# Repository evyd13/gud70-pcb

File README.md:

# Gud70 PCB

This is a replacement PCB for the Uniqey C70. Manufacturing files are included.

Some boards do not come with the LED seperator thingy, to prevent light bleed, so there is one that can be 3d printed as well.

Please read the license before use.

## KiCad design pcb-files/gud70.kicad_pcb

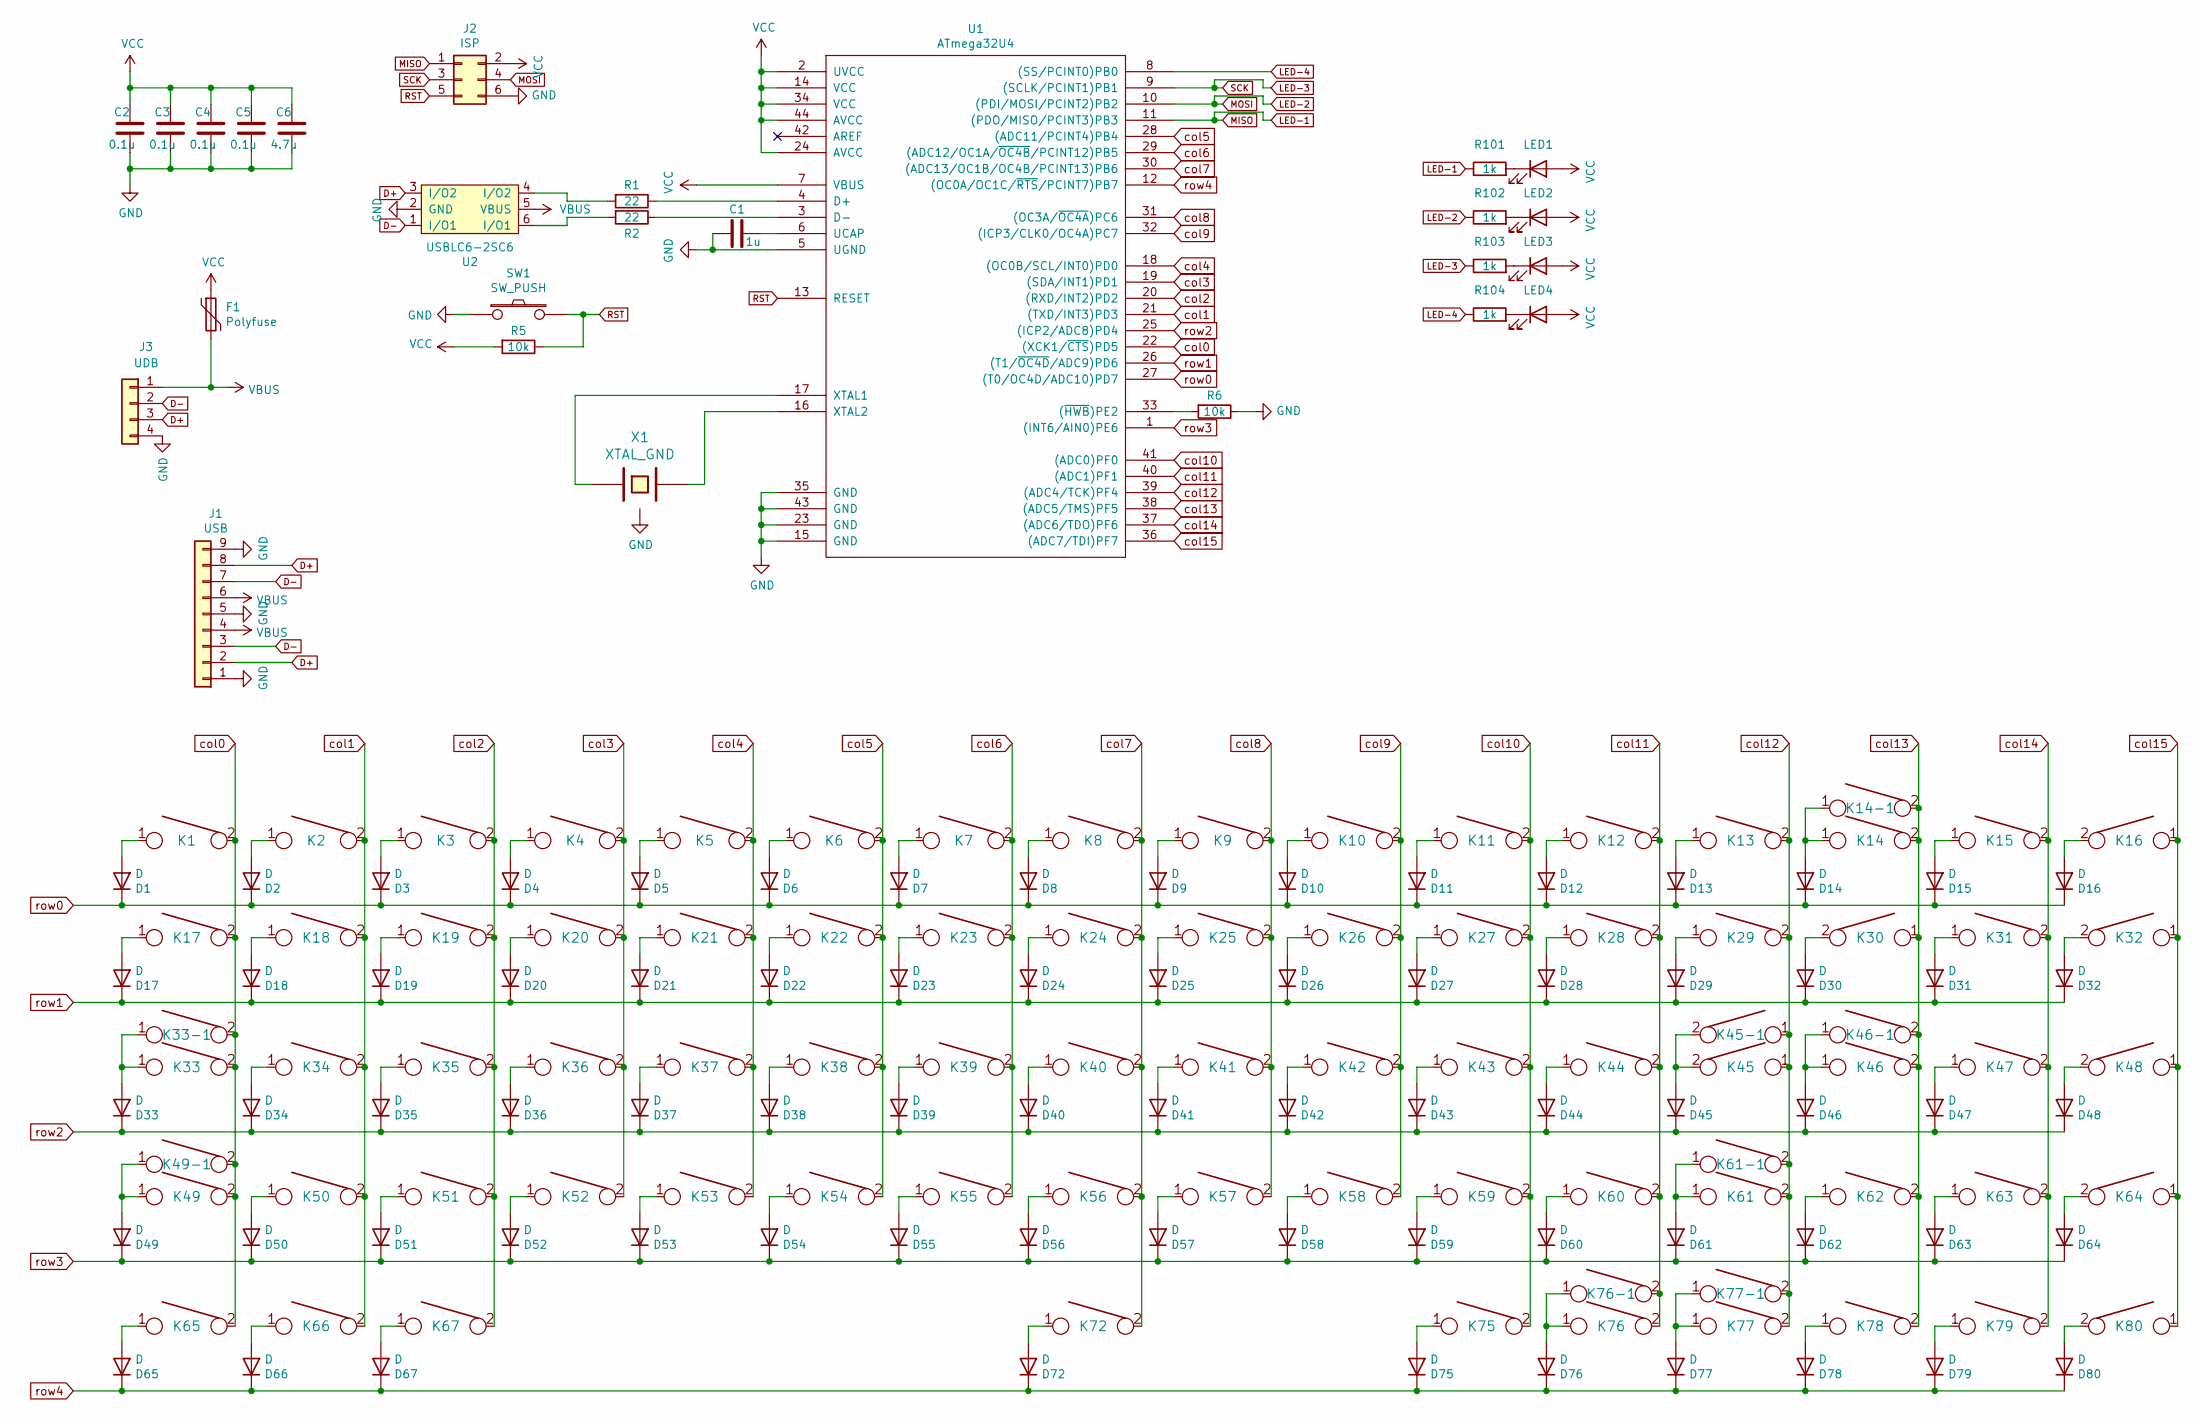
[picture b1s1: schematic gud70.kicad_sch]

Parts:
C1: 1u; C_0805
C2, C3, C4, C5: 0.1u; C_0805
C6: 4.7u; C_0805
D1, D2, D3, D4, D5, D6, D7, D8, D9, D10, D11, D12, D13, D14, D15, D16, D17, D18, D19, D20, D21, D22, D23, D24, D25, D26, D27, D28, D29, D30, D31, D32, D33, D34, D35, D36, D37, D38, D39, D40, D41, D42, D43, D44, D45, D46, D47, D48, D49, D50, D51, D52, D53, D54, D55, D56, D57, D58, D59, D60, D61, D62, D63, D64, D65, D66, D67, D72, D75, D76, D77, D78, D79, D80: D; hybrid_DIODE_sans
F1: Polyfuse; R_0805
J1: USB; PinHeader_1x09_P2.54mm_Vertical
J2: ISP; isp_standard
J3: UDB; JST_SH_SM04B-SRSS-TB_1x04-1MP_P1.00mm_Horizontal; JLCPCB BOM 0
K1, K2, K3, K4, K5, K6, K7, K8, K9, K10, K11, K12, K13, K14-1, K15, K16, K18, K19, K20, K21, K22, K23, K24, K25, K26, K27, K28, K29, K30, K31, K32, K34, K35, K36, K37, K38, K39, K40, K41, K42, K43, K44, K45, K47, K48, K50, K51, K52, K53, K54, K55, K56, K57, K58, K59, K60, K62, K63, K64, K66, K76, K77-1, K78, K79, K80: KEYSW; CHERRY_PLATE_100H
K14: KEYSW; CHERRY_PCB_200H
K17, K45-1, K65, K67, K75, K76-1, K77: KEYSW; CHERRY_PLATE_150H
K33, K61: KEYSW; CHERRY_PLATE_175H
K33-1, K49-1: KEYSW; CHERRY_PLATE_125H
K46, K49: KEYSW; CHERRY_PCB_225H
K46-1: KEYSW; CHERRY_PCB_200H_V
K61-1: KEYSW; CHERRY_PCB_275H
K72: KEYSW; CHERRY_PCB_600H_F
LED1, LED2, LED3, LED4: LED; smd_led; Part 27-21/W1D-ANPHY/3C
R1, R2: 22; R_0805
R5, R6: 10k; R_0805
R101, R102, R103, R104: 1k; R_0805
SW1: SW_PUSH; SW_SPST_TL3342
U1: ATmega32U4; ATMEGA32U4
U2: USBLC6-2SC6; Farnell 1295310
X1: XTAL_GND; Resonator_SMD_muRata_CSTNExxV-3Pin-p1.2

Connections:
D+: J1.2, J1.8, J3.3, U2.3 (I/O2)
D-: J1.3, J1.7, J3.2, U2.1 (I/O1)
GND: C1.2, C2.1, C3.1, C4.1, C5.1, C6.1, J1.1, J1.5, J1.9, J2.6, J3.4, R6.1, SW1.1, U1.5 (UGND), U1.15 (GND), U1.23 (GND), U1.35 (GND), U1.43 (GND), U2.2 (GND), X1.3
LED-1: J2.1, R101.1, U1.11 ((PDO/MISO/PCINT3)PB3)
LED-2: J2.4, R102.1, U1.10 ((PDI/MOSI/PCINT2)PB2)
LED-3: J2.3, R103.1, U1.9 ((SCLK/PCINT1)PB1)
LED-4: R104.1, U1.8 ((SS/PCINT0)PB0)
unnamed: C1.1, U1.6 (UCAP)
unnamed: D1.2 (A), K1.1
unnamed: D2.2 (A), K2.1
unnamed: D3.2 (A), K3.1
unnamed: D4.2 (A), K4.1
unnamed: D5.2 (A), K5.1
unnamed: D6.2 (A), K6.1
unnamed: D7.2 (A), K7.1
unnamed: D8.2 (A), K8.1
unnamed: D9.2 (A), K9.1
unnamed: D10.2 (A), K10.1
unnamed: D11.2 (A), K11.1
unnamed: D12.2 (A), K12.1
unnamed: D13.2 (A), K13.1
unnamed: D14.2 (A), K14.1, K14-1.1
unnamed: D15.2 (A), K15.1
unnamed: D16.2 (A), K16.2
unnamed: D17.2 (A), K17.1
unnamed: D18.2 (A), K18.1
unnamed: D19.2 (A), K19.1
unnamed: D20.2 (A), K20.1
unnamed: D21.2 (A), K21.1
unnamed: D22.2 (A), K22.1
unnamed: D23.2 (A), K23.1
unnamed: D24.2 (A), K24.1
unnamed: D25.2 (A), K25.1
unnamed: D26.2 (A), K26.1
unnamed: D27.2 (A), K27.1
unnamed: D28.2 (A), K28.1
unnamed: D29.2 (A), K29.1
unnamed: D30.2 (A), K30.2
unnamed: D31.2 (A), K31.1
unnamed: D32.2 (A), K32.2
unnamed: D33.2 (A), K33.1, K33-1.1
unnamed: D34.2 (A), K34.1
unnamed: D35.2 (A), K35.1
unnamed: D36.2 (A), K36.1
unnamed: D37.2 (A), K37.1
unnamed: D38.2 (A), K38.1
unnamed: D39.2 (A), K39.1
unnamed: D40.2 (A), K40.1
unnamed: D41.2 (A), K41.1
unnamed: D42.2 (A), K42.1
unnamed: D43.2 (A), K43.1
unnamed: D44.2 (A), K44.1
unnamed: D45.2 (A), K45.2, K45-1.2
unnamed: D46.2 (A), K46.1, K46-1.1
unnamed: D47.2 (A), K47.1
unnamed: D48.2 (A), K48.2
unnamed: D49.2 (A), K49.1, K49-1.1
unnamed: D50.2 (A), K50.1
unnamed: D51.2 (A), K51.1
unnamed: D52.2 (A), K52.1
unnamed: D53.2 (A), K53.1
unnamed: D54.2 (A), K54.1
unnamed: D55.2 (A), K55.1
unnamed: D56.2 (A), K56.1
unnamed: D57.2 (A), K57.1
unnamed: D58.2 (A), K58.1
unnamed: D59.2 (A), K59.1
unnamed: D60.2 (A), K60.1
unnamed: D61.2 (A), K61.1, K61-1.1
unnamed: D62.2 (A), K62.1
unnamed: D63.2 (A), K63.1
unnamed: D64.2 (A), K64.2
unnamed: D65.2 (A), K65.1
unnamed: D66.2 (A), K66.1
unnamed: D67.2 (A), K67.1
unnamed: D72.2 (A), K72.1
unnamed: D75.2 (A), K75.1
unnamed: D76.2 (A), K76.1, K76-1.1
unnamed: D77.2 (A), K77.1, K77-1.1
unnamed: D78.2 (A), K78.1
unnamed: D79.2 (A), K79.1
unnamed: D80.2 (A), K80.2
unnamed: LED1.1 (K), R101.2
unnamed: LED2.1 (K), R102.2
unnamed: LED3.1 (K), R103.2
unnamed: LED4.1 (K), R104.2
unnamed: R1.1, U1.4 (D+)
unnamed: R1.2, U2.4 (I/O2)
unnamed: R2.1, U1.3 (D-)
unnamed: R2.2, U2.6 (I/O1)
unnamed: R6.2, U1.33 ((~HWB~)PE2)
unnamed: U1.16 (XTAL2), X1.2
unnamed: U1.17 (XTAL1), X1.1
RST: J2.5, R5.1, SW1.2, U1.13 (RESET)
VBUS: F1.2, J1.4, J1.6, J3.1, U2.5 (VBUS)
VCC: C2.2, C3.2, C4.2, C5.2, C6.2, F1.1, J2.2, LED1.2 (A), LED2.2 (A), LED3.2 (A), LED4.2 (A), R5.2, U1.2 (UVCC), U1.7 (VBUS), U1.14 (VCC), U1.24 (AVCC), U1.34 (VCC), U1.44 (AVCC)
col0: K1.2, K17.2, K33.2, K33-1.2, K49.2, K49-1.2, K65.2, U1.22 ((XCK1/~CTS~)PD5)
col1: K2.2, K18.2, K34.2, K50.2, K66.2, U1.21 ((TXD/INT3)PD3)
col2: K3.2, K19.2, K35.2, K51.2, K67.2, U1.20 ((RXD/INT2)PD2)
col3: K4.2, K20.2, K36.2, K52.2, U1.19 ((SDA/INT1)PD1)
col4: K5.2, K21.2, K37.2, K53.2, U1.18 ((OC0B/SCL/INT0)PD0)
col5: K6.2, K22.2, K38.2, K54.2, U1.28 ((ADC11/PCINT4)PB4)
col6: K7.2, K23.2, K39.2, K55.2, U1.29 ((ADC12/OC1A/~OC4B~/PCINT12)PB5)
col7: K8.2, K24.2, K40.2, K56.2, K72.2, U1.30 ((ADC13/OC1B/OC4B/PCINT13)PB6)
col8: K9.2, K25.2, K41.2, K57.2, U1.31 ((OC3A/~OC4A~)PC6)
col9: K10.2, K26.2, K42.2, K58.2, U1.32 ((ICP3/CLK0/OC4A)PC7)
col10: K11.2, K27.2, K43.2, K59.2, K75.2, U1.41 ((ADC0)PF0)
col11: K12.2, K28.2, K44.2, K60.2, K76.2, K76-1.2, U1.40 ((ADC1)PF1)
col12: K13.2, K29.2, K45.1, K45-1.1, K61.2, K61-1.2, K77.2, K77-1.2, U1.39 ((ADC4/TCK)PF4)
col13: K14.2, K14-1.2, K30.1, K46.2, K46-1.2, K62.2, K78.2, U1.38 ((ADC5/TMS)PF5)
col14: K15.2, K31.2, K47.2, K63.2, K79.2, U1.37 ((ADC6/TDO)PF6)
col15: K16.1, K32.1, K48.1, K64.1, K80.1, U1.36 ((ADC7/TDI)PF7)
row0: D1.1 (K), D2.1 (K), D3.1 (K), D4.1 (K), D5.1 (K), D6.1 (K), D7.1 (K), D8.1 (K), D9.1 (K), D10.1 (K), D11.1 (K), D12.1 (K), D13.1 (K), D14.1 (K), D15.1 (K), D16.1 (K), U1.27 ((T0/OC4D/ADC10)PD7)
row1: D17.1 (K), D18.1 (K), D19.1 (K), D20.1 (K), D21.1 (K), D22.1 (K), D23.1 (K), D24.1 (K), D25.1 (K), D26.1 (K), D27.1 (K), D28.1 (K), D29.1 (K), D30.1 (K), D31.1 (K), D32.1 (K), U1.26 ((T1/~OC4D~/ADC9)PD6)
row2: D33.1 (K), D34.1 (K), D35.1 (K), D36.1 (K), D37.1 (K), D38.1 (K), D39.1 (K), D40.1 (K), D41.1 (K), D42.1 (K), D43.1 (K), D44.1 (K), D45.1 (K), D46.1 (K), D47.1 (K), D48.1 (K), U1.25 ((ICP2/ADC8)PD4)
row3: D49.1 (K), D50.1 (K), D51.1 (K), D52.1 (K), D53.1 (K), D54.1 (K), D55.1 (K), D56.1 (K), D57.1 (K), D58.1 (K), D59.1 (K), D60.1 (K), D61.1 (K), D62.1 (K), D63.1 (K), D64.1 (K), U1.1 ((INT6/AIN0)PE6)
row4: D65.1 (K), D66.1 (K), D67.1 (K), D72.1 (K), D75.1 (K), D76.1 (K), D77.1 (K), D78.1 (K), D79.1 (K), D80.1 (K), U1.12 ((OC0A/OC1C/~RTS~/PCINT7)PB7)

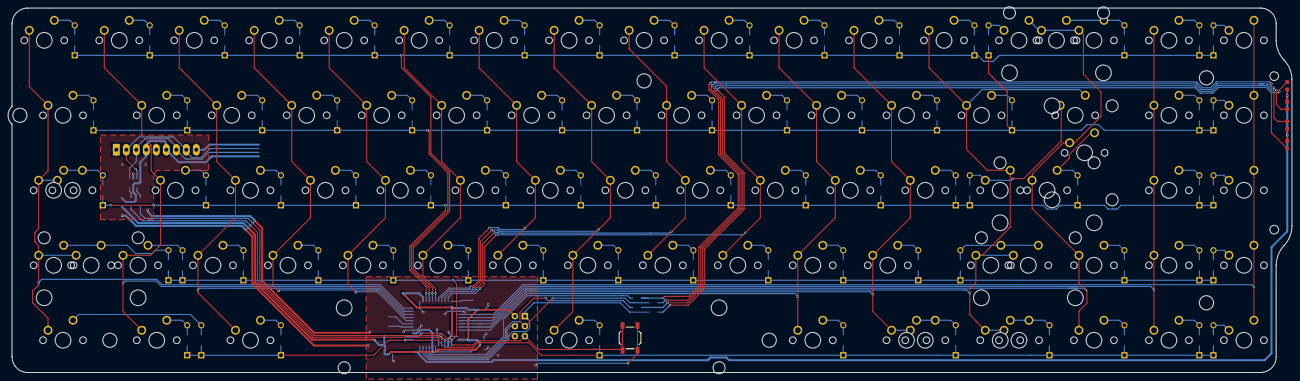
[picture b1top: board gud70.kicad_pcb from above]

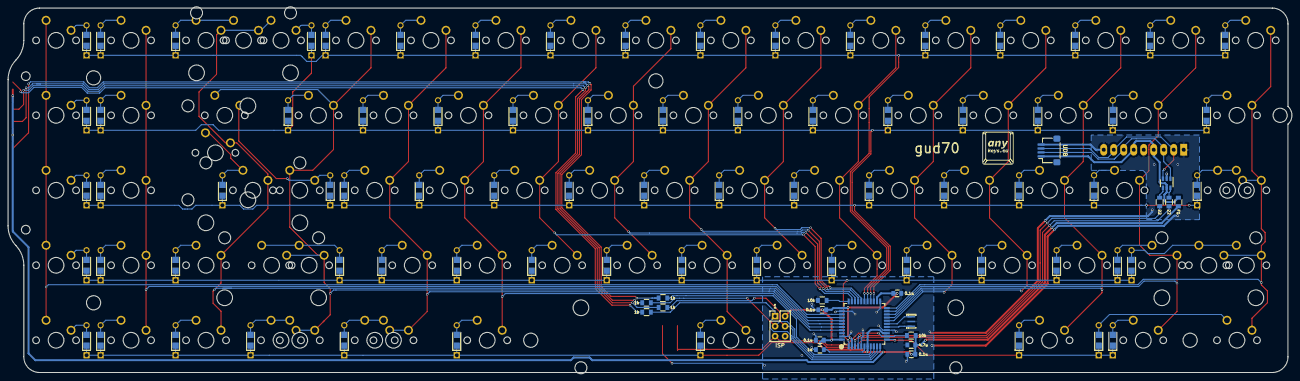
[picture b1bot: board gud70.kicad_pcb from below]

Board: 2 copper layers, 326.2 x 92.6 mm, 182 parts (94 on the bottom side), 117 nets.

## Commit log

2021-02-24 Upload files
2021-02-24 Upload license and readme
